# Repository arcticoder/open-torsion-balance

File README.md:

# open-torsion-balance

An open, low-cost torsion balance for measuring small forces in air, with printable mechanics, a force-noise model checked against published balances, fab-assembled electronics and a documented loop that feeds each campaign's calibration data back into the instrument's metrology ([docs/campaign_loop.md](docs/campaign_loop.md)).

**The instrument.** A horizontal arm on a taut stainless strip, read optically and calibrated electrostatically and by added inertia, with a resolution target of 0.4 nN (5σ on a 20 nN term) in a 1000 s measurement, at a parts cost to be filled in from the final bill of materials. Every noise term is predicted from a parameter file (`hardware/balance/params.py`), and every parameter that a measurement replaces will be recorded with the run that set it (the provenance table is designed, not built).

**The first campaign: the question.** On an open, fully SMT-assembled, low-cost torsion balance operating in air, quantify the
forces that usually pass for thrust: the Lorentz force of supply-lead currents in the ambient magnetic field,
and the thermal and convective forces of a dissipating device. Measure them as functions of current, lead
geometry and dissipated power, with the balance's force noise floor, calibration constant and drift fully
characterized. The instrument claim is a resolution of 0.4 nN or better (5σ on a 20 nN term) in a 1000 s
measurement.

**Next campaigns.** Materials and geometry for the frame and damper, chosen by simulation and checked by injected-signal transfer coefficients, so improvements are measured in air before any vacuum work ([docs/scope_and_rename.md](docs/scope_and_rename.md)).

## Status

| Piece | State |
|---|---|
| G1 measurement goal | confirmed 2026-10-23 |
| G2 mechanics | an FR4 arm board on edge hung from a torsion head, collision-free over the swing, centre of mass solved onto the axis; JLC mechanical boards (the arm, electrode and clamp boards are ordered; the electrode and ground-clamp boards have arrived); printed PLA enclosure (1.2 mm plates with a 2 mm rim, no window); field-modelled eddy damper; cutting jigs; [fabrication decisions](docs/fabrication.md), [assembly steps](docs/assembly.md) |
| G3 force-noise prediction | 0.108 nN (1σ, 1000 s, in air): a conditional go |
| WP1–WP3: requirements, 50 JLC-stocked parts, analog block simulations | done |
| WP4 schematic | done as checked netlists (main board + four head boards, 50 JLC parts); readable sheet rendering is in the backlog |
| WP5 main-board layout | done to the DFM gate (120 x 90 mm, 4 layers, routed); fab files in `hardware/instrument/fab/` (Gerbers, BOM, CPL, `ORDER.md`) |
| Main-board order | route decided (Economic PCBA, 2 boards assembled, LIS2DW12 not placed on the first articles); placed 2026-11-18, in production at JLC (Economic PCBA, 2 assembled, LIS2DW12 not placed) |
| A5: prototype noise measurement | after the board arrives and passes bring-up (`docs/bringup.md`); it runs on the assembled board, not on breadboards |

The prediction is dominated by air currents (4.8 nN/√Hz), so the verdict flips at about 4 mm/s of air-speed
fluctuation; the enclosure is the biggest noise control. The model reproduces six published numbers, from
Soni and Roy (Rev. Sci. Instrum. 84, 095103, 2013) and the cryogenic torsion balance of arXiv:2206.02890.

## Layout

| Path | What |
|---|---|
| `docs/plan.md` | the plan: goal, mechanics, noise budget, environment control, calibration |
| `docs/fabrication.md`, `docs/assembly.md` | how each part is made (fab boards, PLA, bought; JLC orders, coupons and parcels) and how to build it |
| `docs/bringup.md`, `docs/procedures.md` | powering up the electronics step by step; the prototype check, calibration and measurement campaign |
| `docs/paper/` | the paper skeleton (LaTeX; results are placeholders) |
| `hardware/balance/` | parametric CAD (`balance.py`, STL and STEP in `cad/`), the FR4 boards for JLC (`boards.py`, `boards/fab/`), jigs, analytic model, parameters, checks |
| `hardware/instrument/` | the electronics: requirements, pin map, parts table, ngspice simulations, checks |
| `hardware/tools/jlc_query.py` | search of the JLCPCB parts snapshot |
| `tools/force_noise_budget.py` | the force-noise prediction and the anchor checks |
| `docs/TODO-agent.md`, `docs/TODO-arcticoder.md` | the work lists (`TODO-BLOCKED.md`, `TODO-backlog.md`, `TODO-completed.md` beside them) |

## Running the checks

Setup (Linux/WSL) is in [hardware/README.md](hardware/README.md): KiCad 9, a Python venv with CadQuery,
SKiDL and ngspice.

```
python3 tools/force_noise_budget.py                       # the noise prediction and anchor checks
~/.venvs/lab-hw/bin/python tools/run_all_smoke_tests.py   # CAD, pin map, power budget, simulations
```

## Construction rules

- Every electronic part is a machine-placed SMT part from JLCPCB's own library; nothing is hand-soldered
  and nothing is mailed to the fab.
- USB power only; nothing above 50 V DC or 30 V AC. The device current is capped at 300 mA by the USB budget.
- The balance carries no permanent magnet on the moving arm (a 6 × 3 mm N42 disc alone would add about
  7 nN/√Hz of field noise); masses on the arm are brass or plastic.

## Companion circuits

The bench circuits this experiment uses for its prototype check (lock-in amplifier, optical shadow readout,
R-2R signal generator) live in [arcticoder/lab](https://github.com/arcticoder/lab), which also holds the shared
parts inventory and order ledger.

## License

- **Code** (MIT, [LICENSE](LICENSE)): the Python sources, including the CadQuery scripts and the noise model.
- **Hardware designs and their documentation** (CERN-OHL-P v2, [LICENSE-HARDWARE](LICENSE-HARDWARE)): the CAD outputs (STL, STEP), KiCad
  files when they exist, SPICE netlists, parts tables and BOMs, and the assembly and design documents. A CadQuery `.py` file is code (MIT)
  whose output is hardware (CERN-OHL-P).

Scope and next steps: [docs/campaign_loop.md](docs/campaign_loop.md) (measurement-to-improvement loop) and [docs/scope_and_rename.md](docs/scope_and_rename.md) (the repo is being generalised).

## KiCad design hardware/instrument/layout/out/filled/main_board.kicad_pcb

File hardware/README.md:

# hardware/ — the force balance and its fab-assembled electronics

The plan is in [docs/plan.md](../docs/plan.md); the user's task list is
[docs/TODO-arcticoder.md](../docs/TODO-arcticoder.md) and the original Part A planning is archived in
[docs/kb/part_a_planning_archive.md](../docs/kb/part_a_planning_archive.md).

| Folder | Contents |
|--------|----------|
| `balance/` | The torsion balance: `params.py` (single source of numbers), `model.py` (analytic model), `balance.py` (CadQuery CAD, exports `cad/*.stl` and `balance.step`), `boards.py` (the FR4 boards as KiCad files, DRC, Gerbers: `boards/` and `boards/fab/`), `fixtures.py` (printed cutting and setting jigs), `render.py` (PNG views), `smoke_test.py` |
| `tools/` | `jlc_query.py`: search the JLCPCB parts library snapshot for stock, price, basic/extended and whether a part is machine-placed |
| `instrument/` | The fab-assembled electronics: requirements, parts (50 part numbers, `parts.py`), `schematic/` (SKiDL netlists, checked), `layout/` (main-board KiCad layout, routed to the DFM gate), `fab/` (Gerbers, BOM, CPL and `ORDER.md` for the JLC order), `heads_panel/` (optional sensor-head PCBA panel), `firmware/` (MicroPython drivers tested on the host), `host/` (stream decoder, logger, noise analysis), `smoke_test.py` |

`tools/force_noise_budget.py` (top-level `tools/`) is the force-noise prediction (gate G3).

## Toolchain (set up 2026-10-22; nothing here is in the repo's git history except the scripts)

| Piece | Where | How it got there |
|-------|-------|------------------|
| KiCad 9.0.9 and `kicad-cli` | `/usr/bin` | installed by the user from the KiCad 9 PPA on 2026-10-23; the CLI has `sch erc`, `pcb drc`, `pcb render` and the Gerber/drill/BOM exports. The symbol and footprint library packages are still 7.0.11 |
| Python environment | `~/.venvs/lab-hw` | `/usr/bin/python3 -m venv --system-site-packages ~/.venvs/lab-hw`; the system site packages carry `pcbnew` (KiCad's Python module, version 9.0.9 since the upgrade) |
| `skidl`, `kiutils`, `easyeda2kicad`, `cadquery`, `numpy`, `scipy`, `matplotlib`, `magpylib` 6.0.0 | the venv | `~/.venvs/lab-hw/bin/pip install skidl kiutils easyeda2kicad cadquery numpy scipy matplotlib magpylib` (magpylib models the damper magnets' field) |
| Freerouting 2.5.0 (autorouter) | `~/tools/freerouting/freerouting-2.5.0-linux-x64/bin/freerouting` | the release zip (it bundles its own Java 25 runtime; the system's Java 21 can't run the plain jar). Headless: `-de in.dsn -do out.ses -mp 20` |
| JLC parts snapshot | `~/jlcparts/cache.sqlite3` (1.6 GB) | `https://yaqwsx.github.io/jlcparts/data/cache.z01 .. cache.z04` and `cache.zip` (a split zip with no `unzip` available: reassemble with a short Python script that adds each disk's offset, see `docs/kb/pcb_toolchain_notes.md`). Refresh before an order: stock and prices are a daily snapshot |
| ngspice | `/usr/bin/ngspice` | already installed; used for every analog block |

Run the CAD and the combined smoke test with the venv's Python:
`~/.venvs/lab-hw/bin/python hardware/balance/smoke_test.py` (with the system Python the CAD checks
are skipped, not failed).

**Electrical and design rules checks.** `kicad-cli sch erc` and `kicad-cli pcb drc` run from the command line (KiCad 9.0.9); `kicad-cli pcb render` gives the images for the WP6 visual review.

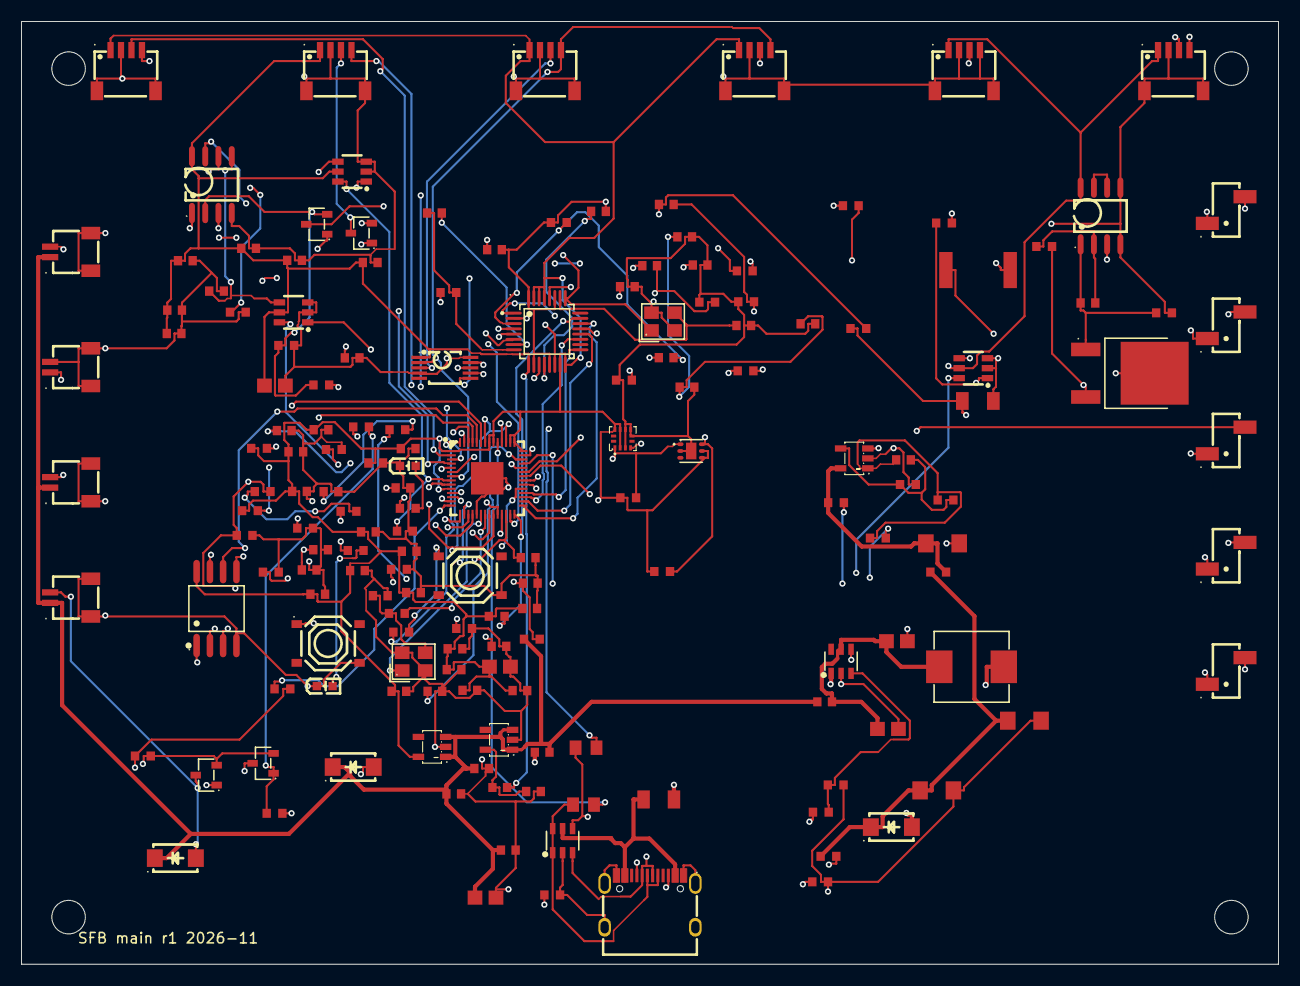
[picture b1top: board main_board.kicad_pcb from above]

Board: 4 copper layers, 120.0 x 90.0 mm, 168 parts (0 on the bottom side), 111 nets.

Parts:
C1, C5, C8, C51, C52: CL21A106KAYNNNE; C0805
C2, C9, C10, C11, C12, C13, C14, C15, C18, C19, C22, C23, C24, C25, C26, C28, C30, C31, C32, C33, C38, C46, C47, C57, C58, C59, C60: CC0603KRX7R9BB104; C0603
C3, C4, C6, C7, C16, C17, C27, C29, C34, C35, C36, C37, C39: CL10A105KB8NNNC; C0603
C20, C21: CL10C150JB8NNNC; C0603
C40, C41: CL10C220JB8NNNC; C0603
C42, C43, C44, C45: CL10B102KB8NNNC; C0603
C48, C49, C56: CL10C100JB8NNNC; C0603
C50: 0603B103K500NT; C0603
C53, C54, C55: CC1206KKX7R9BB475; C1206
CN1, CN2, CN3, CN8, CN9, CN10: SM04B-SRSS-TB; CONN-SMD_4P-P1.00_SM04B-SRSS-TB-LF-SN
CN4, CN5, CN6, CN7: SM02B-SRSS-TB; CONN-SMD_2P-P1.00_SM02B-SRSS-TB-LF-SN
D1: USBLC6-2SC6; SOT-23-6_L2.9-W1.6-P0.95-LS2.8-BL
D2, D3, D4: SS14; SMA_L4.2-W2.6-LS5.0-RD_1
F1: SMD1206P075TF; F1206
H1, H2, H3, H4, H5: HX PZ2.54-1X2P TP-YQ; HDR-SMD_HX-PZ2.54-1X2P-TP-YQ
L1, L2: GZ1608D601TF; L0603
L3: BLM18PG121SN1D_C14709; L0603
L4: SMMS0630-220M; IND-SMD_L7.3-W6.6_MHCI06030
LED1, LED2: KT-0603R; LED-SMD_L1.6-W0.8-R-RD
MH1, MH2, MH3, MH4: M3 hole; MountingHole_M3
Q1, Q2, Q4, Q5: AO3400A; SOT-23-3_L2.9-W1.3-P1.90-LS2.4-BR
Q3: AOD4184A; TO-252-2_L6.6-W6.1-P4.57-LS9.9-TL-CW
R1, R2, R36: 0603WAF5101T5E; R0603
R3, R4: 0805W8F270JT5E; R0805
R5, R6, R7, R8, R14, R15, R16, R17, R18, R19, R20, R21, R28, R29, R46, R49, R50, R52: 0603WAF1001T5E; R0603
R9, R10: 0603WAF2201T5E; R0603
R11, R13, R27, R39, R43, R45, R47, R48: 0603WAF1002T5E; R0603
R12, R22, R24, R26, R30, R33, R34, R35, R42, R44, R51, R53: 0603WAF1003T5E; R0603
R23, R25, R37, R40, R41: 0603WAF510JT5E; R0603
R31: 1206W4F100KT5E; R1206
R32: 25121WJ047JT4E; R2512
R38: 0603WAF4702T5E; R0603
SW1, SW2: TS-1187A-B-A-B; SW-SMD_4P-L5.1-W5.1-P3.70-LS6.5-TL_H1.5
U1, U2: LP5907MFX-3.3/NOPB; SOT-23-5_L3.0-W1.7-P0.95-LS2.8-BR
U3: RP2040; LQFN-56_L7.0-W7.0-P0.4-EP
U4: ABM8-272-T3_C20625731; CRYSTAL-SMD_4P-L3.2-W2.5-BL
U5: W25Q16JVSSIQTR; SOIC-8_L5.3-W5.3-P1.27-LS8.0-BL
U6: TMP117AIDRVR; WSON-6_L2.0-W2.0-P0.65-TL-EP
U7: LIS2DW12TR; LGA-12_L2.0-W2.0-P0.50-BL
U8: MCP4728-E/UN; MSOP-10_L3.0-W3.0-P0.50-LS5.0-TL
U9: ADS131A04IPBSR; TQFP-32_L5.0-W5.0-P0.50-LS7.0-TL
U10, U11: TLV9062IDR; SOIC-8_L5.0-W4.0-P1.27-LS6.0-BL
U12, U13, U14: SN74LVC1G3157DBVR; SOT-23-6_L2.9-W1.6-P0.95-LS2.8-BR
U15: MT3608; SOT-23-6_L2.9-W1.6-P0.95-LS2.8-BL
U16: OPA197IDBVR; SOT-23-5_L3.0-W1.7-P0.95-LS2.8-BR
USBC1: TYPE-C-31-M-12; USB-C_SMD-TYPE-C-31-M-12_1
X1: X322512MSB4SI; CRYSTAL-SMD_4P-L3.2-W2.5-BL

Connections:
3V3_A: C8.1, C27.1, C28.1, C29.1, C30.1, C46.1, C47.1, CN8.1, CN9.1, CN10.1, L2.2, U8.1, U9.9, U10.8, U11.8, U12.5, U13.5, U14.5
3V3_AR: C7.1, L2.1, U2.5
3V3_D: C4.1, C5.1, C9.1, C10.1, C11.1, C12.1, C13.1, C14.1, C15.1, C16.1, C22.1, C24.1, C25.1, C26.1, C36.1, C37.1, C38.1, CN1.1, CN2.1, CN3.1, R9.1, R10.1, R11.1, R12.1, R13.1, U1.5, U3.1, U3.10, U3.22, U3.33, U3.42, U3.43, U3.44, U3.48, U3.49, U5.8, U6.4, U6.5, U7.2, U7.9, U7.10, U9.15, U9.16, U9.29, U9.30, U9.31
ADC_CAP: C39.1, U9.28
ADC_CS: R13.2, U3.28, U9.23
ADC_DRDY: U3.31, U9.19
ADC_IN1N: C42.2, R15.2, U9.1
ADC_IN1P: C42.1, R14.2, U9.2
ADC_IN2N: C43.2, R17.2, U9.3
ADC_IN2P: C43.1, R16.2, U9.4
ADC_IN3N: C44.2, R19.2, U9.5
ADC_IN3P: C44.1, R18.2, U9.6
ADC_IN4N: C45.2, R21.2, U9.7
ADC_IN4P: C45.1, R20.2, U9.8
ADC_MISO: R12.2, U3.27, U9.21
ADC_MOSI: U3.30, U9.20
ADC_REFEXT: C35.1, U9.14
ADC_REFP: C34.1, U9.12
ADC_RESET: R11.2, U3.32, U9.17
ADC_SCK: U3.29, U9.22
ADC_VNCP: C31.1, C32.1, C33.1, U9.11
ADC_XTAL1: C40.1, U9.25, X1.1
ADC_XTAL2: C41.1, U9.26, X1.3
BOOST_EN: R33.1, U3.16, U15.4
BOOST_FB: R35.2, R36.1, U15.3
BOOST_FB_MID: R34.2, R35.1
BOOST_SW: D2.2, L4.2, U15.1
BOOTSEL_N: R6.2, SW1.1
CC1: R1.1, USBC1.A5
CC2: R2.1, USBC1.B5
DAC_DUT: R27.1, U8.8
DAC_LED1: U8.6, U12.1
DAC_LED2: U8.9, U13.1
DAC_PLATE: U8.7, U16.3
DEBUG_RX: CN1.4, U3.3
DEBUG_TX: CN1.3, U3.2
DUT_D: Q3.2, R32.1
DUT_DIV: R27.2, R28.1, U14.1
DUT_EN: R26.1, U3.15, U14.6
DUT_FB: C50.2, R29.1, U11.2
DUT_G: C50.1, Q3.1, R30.1, U11.1
DUT_RET: CN4.2, R32.2
DUT_SET: U11.3, U14.4
DVDD_1V1: C17.1, C18.1, C19.1, U3.23, U3.45, U3.50
GND: C1.2, C2.2, C3.2, C4.2, C5.2, C6.2, C7.2, C8.2, C9.2, C10.2, C11.2, C12.2, C13.2, C14.2, C15.2, C16.2, C17.2, C18.2, C19.2, C20.2, C21.2, C22.2, C23.2, C24.2, C25.2, C26.2, C27.2, C28.2, C29.2, C30.2, C31.2, C32.2, C33.2, C34.2, C35.2, C36.2, C37.2, C38.2, C39.2, C40.2, C41.2, C46.2, C47.2, C48.2, C49.2, C51.2, C52.2, C53.2, C54.2, C55.2, C57.2, C58.2, C59.2, C60.2, CN1.2, CN1.5, CN1.6, CN2.2, CN2.5, CN2.6, CN3.2, CN3.5, CN3.6, CN4.3, CN4.4, CN5.2, CN5.3, CN5.4, CN6.3, CN6.4, CN7.3, CN7.4, CN8.2, CN8.4, CN8.5, CN8.6, CN9.2, CN9.5, CN9.6, CN10.2, CN10.5, CN10.6, D1.2, LED1.2, LED2.2, Q4.2, Q5.2, R1.2, R2.2, R15.1, R17.1, R19.1, R21.1, R22.2, R23.2, R24.2, R25.2, R26.2, R28.2, R30.2, R31.2, R33.2, R36.2, R39.2, R43.2, R45.2, R48.2, R51.2, R53.2, SW1.4, SW2.4, U1.2, U2.2, U3.19, U3.57, U4.2, U4.4, U5.4, U6.2, U6.7, U7.3, U7.6, U7.7, U7.8, U8.4, U8.10, U9.10, U9.13, U9.27, U9.32, U10.4, U11.4, U11.5, U12.2, U12.3, U13.2, U13.3, U14.2, U14.3, U15.2, U16.2, USBC1.1, USBC1.2, USBC1.3, USBC1.4, USBC1.A1B12, USBC1.B1A12, X1.2, X1.4
I2C_SCL: CN2.4, CN3.4, R10.2, U3.7, U6.1, U7.1, U8.2
I2C_SDA: CN2.3, CN3.3, R9.2, U3.6, U6.6, U7.4, U8.3
LED1_G: Q1.1, U10.1
LED1_K: CN9.3, Q1.3
LED1_MOD: R22.1, U3.8, U12.6
LED1_REF: C48.1, U10.3, U12.4
LED1_SRC: Q1.2, R23.1, R49.1, U10.2
LED2_G: Q2.1, U10.7
LED2_K: CN10.3, Q2.3
LED2_MOD: R24.1, U3.9, U13.6
LED2_REF: C49.1, U10.5, U13.4
LED2_SRC: Q2.2, R25.1, U10.6
MON_5V: C59.1, R47.2, R48.1, U3.39
MON_24V: C58.1, R46.2, U3.38
MON_LED: C60.1, R49.2, U3.40
MON_SPARE: CN10.4, U3.41
MOTOR1_D: CN6.2, D3.2, Q4.3
MOTOR1_G: Q4.1, R50.2, R51.1
MOTOR1_PWM: R50.1, U3.13
MOTOR2_D: CN7.2, D4.2, Q5.3
MOTOR2_G: Q5.1, R52.2, R53.1
MOTOR2_PWM: R52.1, U3.14
PD_SIG: CN8.3, R14.1
PLATE_FB: C56.2, R38.2, R39.1, U16.4
PLATE_MON: C57.1, R20.1, R42.2, R43.1
PLATE_OP: C56.1, R38.1, R40.1, U16.1
PLATE_OUT: CN5.1, R41.2, R42.1
PLATE_SR: R40.2, R41.1
QSPI_SCLK: U3.52, U5.6
QSPI_SD0: U3.53, U5.5
QSPI_SD1: U3.55, U5.2
QSPI_SD2: U3.54, U5.3
QSPI_SD3: U3.51, U5.7
QSPI_SS: R6.1, U3.56, U5.1
RAIL_MON: R44.2, R45.1, R46.1
REF_SIG: CN9.4, R16.1
RUN: C23.1, SW2.1, U3.26
SHUNT: Q3.3, R18.1, R29.2, R31.1
SPARE_A: H1.1, U3.4
SPARE_B: H1.2, U3.5
SPARE_C: H2.1, U3.34
SPARE_D: H2.2, U3.35
SPARE_E: H3.1, U3.36
SPARE_F: H3.2, U3.37
SPARE_G: H4.1, U3.11
SPARE_H: H4.2, U3.12
SPARE_OP: U11.6, U11.7
STATUS_LED1: R7.1, U3.17
STATUS_LED1_A: LED1.1, R7.2
STATUS_LED2: R8.1, U3.18
STATUS_LED2_A: LED2.1, R8.2
SWCLK: H5.1, U3.24
SWD: H5.2, U3.25
USB_DM: R4.2, U3.46
USB_DM_C: D1.3, D1.4, R4.1, USBC1.A7, USBC1.B7
USB_DP: R3.2, U3.47
USB_DP_C: D1.1, D1.6, R3.1, USBC1.A6, USBC1.B6
V5: C1.1, C2.1, C3.1, C6.1, CN4.1, CN6.1, CN7.1, D3.1, D4.1, L1.2, L3.1, R47.1, U1.1, U1.3, U2.1, U2.3
V5_BOOST: C51.1, C52.1, L3.2, L4.1, U15.5
V24: C55.1, R37.2, R44.1, U16.5
V24_RAW: C53.1, C54.1, D2.1, R34.1, R37.1
VBUS: D1.5, F1.1, USBC1.A4B9, USBC1.B4A9
VBUS_F: F1.2, L1.1
XIN: C20.1, U3.20, U4.1
XOSC_OUT: C21.1, R5.1, U4.3
XOUT: R5.2, U3.21

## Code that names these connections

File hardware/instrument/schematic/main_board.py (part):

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    gnd += xt[2], xt[4]
    C("15p", xin)
    C("15p", xo)
    R("1k", xo, net("XOUT"), "XOUT damping (guide: 1 kohm)")
    net("XOUT").__iadd__(rp[21])

    # QSPI flash, wired straight to the RP2040
    fl = part(131025, "QSPI flash 16 Mbit")
    for fpin, sig in ((1, "QSPI_SS"), (2, "QSPI_SD1"), (3, "QSPI_SD2"), (5, "QSPI_SD0"), (6, "QSPI_SCLK"), (7, "QSPI_SD3")):
        net(sig).__iadd__(fl[fpin])
    for sig, rpin in (("QSPI_SS", 56), ("QSPI_SD1", 55), ("QSPI_SD2", 54), ("QSPI_SD0", 53), ("QSPI_SCLK", 52), ("QSPI_SD3", 51)):
        net(sig).__iadd__(rp[rpin])
    gnd += fl[4]
    v3d += fl[8]
    C("100n", v3d)

    # BOOTSEL: QSPI_SS through 1 kohm to a switch. The switch's diagonal pins (1 and 4) are always on opposite sides of the contact.
    boot = net("BOOTSEL_N")
    R("1k", net("QSPI_SS"), boot, "QSPI_SS boot strap (guide: 1 kohm)")
    sw_boot = part(318884, "BOOTSEL")
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    net("DEBUG_RX").__iadd__(jd[4])
    gnd += jd[5], jd[6]  # mounting tabs

    # SWD and the spare GPIOs on 2-pin 2.54 mm headers: (A,B) (C,D) (E,F) (G,H), and SWD/SWCLK
    for a, b in (("SPARE_A", "SPARE_B"), ("SPARE_C", "SPARE_D"), ("SPARE_E", "SPARE_F"), ("SPARE_G", "SPARE_H")):
        h = part(41417359, "spare GPIOs")
        net(a).__iadd__(h[1])
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    v3a += sw[5]
    gnd += sw[2], sw[3]
    net("DUT_EN").__iadd__(sw[6])
    R("100k", net("DUT_EN"), gnd, "pulldown while the GPIO floats: current off at reset")
    dut_div = net("DUT_DIV")
    R("10k", dac_c, dut_div, "set-point divider, top")
    R("1k", dut_div, gnd, "set-point divider, bottom")
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    gnd += mt[2]
    bsw += mt[1]
    net("BOOST_EN").__iadd__(mt[4])
    R("100k", net("BOOST_EN"), gnd, "boost off while the GPIO floats")
    ind = part(128694, "boost inductor 22 uH")
    v5b += ind[1]
    bsw += ind[2]
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
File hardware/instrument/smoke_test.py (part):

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adc = {n: g for n, (g, _, _) in P.PINS.items() if n.startswith("MON_")}
check("safety — analog monitors sit only on GP26-GP29 (the ADC inputs)", all(g in P.ADC_PINS for g in adc.values()) and len(adc) == 4, f"{adc}")
slice_of = lambda g: (g >> 1) & 7  # noqa: E731
m1, m2 = P.PINS["MOTOR1_PWM"][0], P.PINS["MOTOR2_PWM"][0]
check("functional — the two motor PWM pins are one slice's A and B outputs", slice_of(m1) == slice_of(m2) and m1 % 2 == 0 and m2 == m1 + 1, f"GP{m1} and GP{m2}, slice {slice_of(m1)}")
check("functional — ADC SPI is SPI0 on GP16-GP19", [P.PINS[n][0] for n in ("ADC_MISO", "ADC_CS", "ADC_SCK", "ADC_MOSI")] == [16, 17, 18, 19], "RX, CSn, SCK, TX")
check("functional — I2C is I2C0 on GP4 and GP5", (P.PINS["I2C_SDA"][0], P.PINS["I2C_SCL"][0]) == (4, 5), "")

for mode in P.MODES:
    i = P.mode_current(mode)
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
